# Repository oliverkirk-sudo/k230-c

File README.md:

# k230-c

## 当前检查点：已恢复 v12 + R2.1 源工程

本仓库保存 CM-K230 核心板的可编辑源工程和验证证据。v12 基线与 R2.1 累积增量均已恢复并核验。**这是原理图/候选封装恢复检查点，不是生产版本。当前候选仍没有完整核心板 PCB。**

当前入口：`project/cad/recovery-physical-candidate/CMK230_Core_REVIEW.kicad_pro`（原理图同名 `.kicad_sch`）。保持 `project/` 内相对目录结构即可解析已恢复的 10 个封装库。

## 本次重新验证（2026-10-03，KiCad 9.0.2）

- v12 ZIP：888 个成员 CRC 通过，886 个原始保留文件哈希匹配；SHA-256 `63dab93b8433b3a367571ec64b11568b9c81dc466e8d562ce2108b647d341e58`
- R2.1 ZIP：332 个成员 CRC 通过，325 个增量文件哈希匹配；SHA-256 `4e23cf611b37900dab169f0b44da5974ae70c65bbcf7624c97ccb16688eb3b5b`
- 增量在独立 v12 工作副本上通过防覆盖校验后应用，全部 325 个增量文件保持一致
- 新导出网表：254 个元件、1,509 个引脚绑定，与 R2.1 归档的元件、属性、网络、引脚功能和类型一致
- 恢复后新 ERC：0 个错误、0 个警告；10 个封装库均能解析
- R528 保持默认 DNP，存储默认禁止；149 个元件有封装字段，105 个仍未分配。R574 封装尚未完成验证

新结果在 `validation/2026-10-03-restored/`。`validation/2026-10-03-delta-only/` 保存基线尚未到达时的历史检查（0 错误、150 个缺库警告）；这些缺库警告已由完整恢复后的新结果取代。`project/` 中其他报告保留历史阶段含义，不能视为本次全部重新执行。

## 尚未完成的工程资格验证

- 当前 `recovery-physical-candidate` 没有完整核心板 PCB；历史 PCB、8 层试验和封装/负控夹具仍保留用于追溯，不是当前 6 层成品
- 38 × 38 mm 外形、140 个触点、1 mm 间距、恰好 6 个铜层及仅顶面贴装是设计要求，并非已达成的制造验收
- 尚需完成封装缺口、整板布局布线、DDR/时序、高温/上电、DFM 和工厂工艺确认
- TI 候选阻焊桥名义 80 µm；NXP 示例名义 55 µm。KiCad 全局最小阻焊桥设为 75 µm 时可能合并开窗。必须核对实际 CAM 与铜/蚀刻/阻焊/钢网/贴装能力

## 发布内容、来源与完整性

`project/` 保留源 CAD、库、脚本、数据、网表、工程审查和来源 URL/哈希，以及必要的 `LICENSE-01studio.txt` 上游 MIT 版权许可声明。未将该许可扩展为对其他第三方材料的新授权。

本公开源文件检查点经过筛选，未包含厂商 PDF/扫描页面、图像、运行时缓存、会话设置、日志、备份 ZIP 及部分大型历史 DDR 搜索生成结果。它不是两个原始 ZIP 的逐字节镜像。历史报告和冻结清单可能引用这些省略文件；需要相关生成结果的旧测试须先重新生成。完整排除项/原始哈希/两处非技术署名编辑见 `PUBLICATION_PROVENANCE.json`；当前发布文件完整性以根目录 `SHA256SUMS` 为准。

## English summary

The verified v12 baseline plus R2.1 delta has been restored. The active editable schematic resolves all 10 footprint libraries. Fresh KiCad 9.0.2 ERC has zero errors and zero warnings; the exported 254-component / 1,509-binding graph matches R2.1. There are 149 assigned and 105 unassigned component footprints. This is a source-recovery checkpoint, not a production release: no complete active six-layer board has been recovered or routed. Historical trials and tests retain their original limited scope.

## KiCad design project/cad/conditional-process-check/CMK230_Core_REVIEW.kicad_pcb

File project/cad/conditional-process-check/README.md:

# Separate conditional process model

This duplicates the current partial/unplaced import for an explicit rule experiment. It is not the production board or an accepted manufacturing recipe. The original 0.20mm-default diagnostic remains in ../high-temp-candidate/partial-pcb-drc-parity.json.

General copper clearance and minimum track width are 0.1016mm. Exactly30 enumerated pad pairs,15 each in U22 and U23, have a0.0762mm conditional pad-to-pad clearance based on source YCG geometry and published advanced process capability. No pad-to-track or arbitrary adjacent copper receives that allowance. The source lands have0.085mm nominal separation, only8.8µm above the proposed local minimum; etch tolerance, mask registration, stencil, assembly and the combined stack/castellation process require acceptance.

The model reports0 geometry violations while retaining138 unrouted items and199 reported missing-footprint issues. The complete source import ledger contains216 missing references. No severity or exclusion was changed. Positive controls confirm both a deliberately intruding listed pad pair and a foreign nearby track are still rejected by their intended rules.

Published advanced fine-line conditions do not automatically apply to the proposed1oz stack or guarantee manufacturing tolerance. Use process-model-manifest.json for exact assumptions and ../engineering references from the project root for the source evidence. Do not treat this as a finished-board DRC pass.

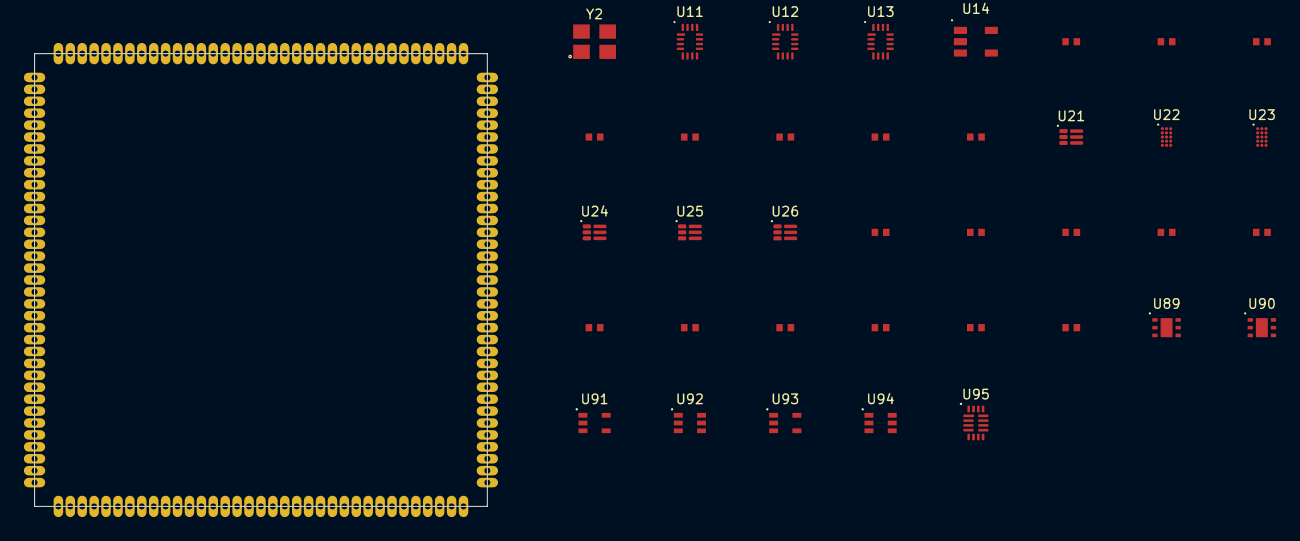
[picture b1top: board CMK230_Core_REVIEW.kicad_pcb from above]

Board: 8 copper layers, 38 parts (0 on the bottom side), 34 nets, no tracks yet.

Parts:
J1: CM-K230 edge contract ONLY; CMK230_38x38_140P1_D0.50_Oval0.80x1.80_PROCESS_UNQUALIFIED
R63, R64, R65, R66: 240R TNPW0402 0.1pct 10ppm TOTAL<=0.70pct CANDIDA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; Vishay_TNPW0402_IPC7351_SourceLand_PROCESS_CANDIDATE
R67, R68: 30k TNPW0402 0.1pct 10ppm TOTAL<=0.70pct CANDIDATE; Vishay_TNPW0402_IPC7351_SourceLand_PROCESS_CANDIDATE
R69, R70, R71: 200R TNPW0402 0.1pct 10ppm TOTAL<=0.70pct CANDIDA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; Vishay_TNPW0402_IPC7351_SourceLand_PROCESS_CANDIDATE
R201: 3.32k TNPW0402 0.1pct 10ppm TOTAL<=0.70pct CANDID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; Vishay_TNPW0402_IPC7351_SourceLand_PROCESS_CANDIDATE
R202, R208, R211, R214, R526: 10k TNPW0402 0.1pct 10ppm TOTAL<=0.70pct CANDIDATE; Vishay_TNPW0402_IPC7351_SourceLand_PROCESS_CANDIDATE
R207: 8.66k TNPW0402 0.1pct 10ppm TOTAL<=0.70pct CANDID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; Vishay_TNPW0402_IPC7351_SourceLand_PROCESS_CANDIDATE
R210: 20k TNPW0402 0.1pct 10ppm TOTAL<=0.70pct CANDIDATE; Vishay_TNPW0402_IPC7351_SourceLand_PROCESS_CANDIDATE
R213: 45.3k TNPW0402 0.1pct 10ppm TOTAL<=0.70pct CANDID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; Vishay_TNPW0402_IPC7351_SourceLand_PROCESS_CANDIDATE
R525: 88.7k TNPW0402 0.1pct 10ppm TOTAL<=0.70pct CANDID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; Vishay_TNPW0402_IPC7351_SourceLand_PROCESS_CANDIDATE
U11, U12, U13: TMUX1574RSVR / CANDIDATE; TI_RSV0016A_TMUX1574_1.8x2.6_P0.4_DrawingVerified
U14: SN74LVC1G32DBVR; TI_DBV0005A_SN74LVC1G32_SOT23_5_DrawingVerified
U21: TPS62827ADMQ; TI_DMQ0006A_TPS6282xA_1.5x1.5_SMD_DrawingVerified
U22, U23: TPS628640BYCGR; TI_YCG0015_TPS628640_1.05x1.78_P0.35_SMD_DrawingVerified
U24, U26: TPS62826ADMQ; TI_DMQ0006A_TPS6282xA_1.5x1.5_SMD_DrawingVerified
U25: TPS62825ADMQ; TI_DMQ0006A_TPS6282xA_1.5x1.5_SMD_DrawingVerified
U89: TPS3808G01DRVR VIN GUARD; TI_DRV0006A_D_TPS3808_6P_EP7_DrawingVerified_CANDIDATE
U90: TPS3808G01DRVR RESET DELAY; TI_DRV0006A_D_TPS3808_6P_EP7_DrawingVerified_CANDIDATE
U91: 74AUP1G17GW,125 HIGH_TEMP CANDIDATE; Nexperia_SOT353-1_AUP1G17_06_DrawingVerified_CANDIDATE
U92, U94: 74AUP1G97GW,125 HIGH_TEMP CANDIDATE; Nexperia_SOT363-2_AUP1G97_DrawingVerified_CANDIDATE
U93: 74AUP1G06GW,125 HIGH_TEMP CANDIDATE; Nexperia_SOT353-1_AUP1G17_06_DrawingVerified_CANDIDATE
U95: NVT4858HKZ TF HS50 CANDIDATE; NXP_SOT1161-2_NVT4858HK_1.8x2.6_P0.4_DrawingVerified_CANDID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
Y2: X322524MOB4SI 24MHz CL12pF CANDIDATE; YXC_X322524MOB4SI_3225_4P_DrawingCandidate

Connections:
CORE_PGOOD_5V: U21.2, U22.E1, U23.E1, U24.1, U25.1, U26.1
DDR_VREF: R65.2, R66.1
DISABLE_OR_TF: U13.13, U14.4
FB_1V8: R210.2, R211.1, U25.3
FB_3V3: R213.2, R214.1, U26.3
FB_CORE: R201.2, R202.1, U21.3
FB_DDR: R207.2, R208.1, U24.3
FIXED_RAILS_PGOOD_3V3: U24.2, U25.2, U26.2, U89.6, U92.3, U94.3
GLOBAL_DISABLE: U11.13, U12.13, U14.1, U93.4
GND: J1.1, J1.2, J1.3, J1.36, J1.49, J1.57, J1.64, J1.71, J1.78, J1.89, J1.106, R64.2, R66.2, R69.2, R70.2, R71.2, R202.2, R208.2, R211.2, R214.2, R526.2, U11.6, U12.6, U12.8, U12.10, U12.11, U12.12, U13.1, U13.4, U13.6, U13.8, U13.11, U13.15, U14.3, U21.4, U22.A1, U22.B1, U22.B2, U22.B3, U23.A1, U23.B1, U23.B2, U23.B3, U24.4, U25.4, U26.4, U89.5, U89.7, U90.5, U90.7, U91.3, U92.1, U92.2, U93.3, U94.1, U94.2, U95.7, Y2.2, Y2.4
MODE_TF: U11.15, U12.15, U14.2
RESET_DELAYED_1V8: U90.6, U91.2
RESET_RELEASE_REQUEST_1V8: U90.4, U94.4
RSTN: J1.122, U94.6
STORAGE_ENABLE_1V8: U92.4, U93.2
SW_CPU: U22.C1, U22.C2, U22.C3
SW_KPU: U23.C1, U23.C2, U23.C3
TFCARD_CLK: J1.21, U95.8
TFCARD_CMD: J1.22, U95.13
TFCARD_D0: J1.17, U95.10
TFCARD_D1: J1.18, U95.9
TFCARD_D2: J1.19, U95.12
TFCARD_D3: J1.20, U95.11
TF_HOST_CLK: U11.1, U95.5
TF_HOST_CMD: U11.4, U95.16
TF_HOST_D0: U11.8, U95.3
TF_HOST_D1: U11.11, U95.4
TF_HOST_D2: U12.1, U95.1
TF_HOST_D3: U12.4, U95.2
VDD1P1_DDR_IO: R63.2, R65.1, R207.1
VDD1P8: J1.8, R210.1, U89.1, U89.4, U90.1, U90.2, U91.5, U92.5, U93.5, U94.5, U95.15
VDD_3V3: J1.7, R213.1, U11.14, U12.14, U13.14, U14.5, U95.14
VIN_5V: J1.4, J1.5, J1.6, R67.1, R68.1, R525.1, U21.6, U22.D1, U22.D2, U22.D3, U23.D1, U23.D2, U23.D3, U24.6, U25.6, U26.6
VIN_GUARD_SENSE: R525.2, R526.1, U89.2

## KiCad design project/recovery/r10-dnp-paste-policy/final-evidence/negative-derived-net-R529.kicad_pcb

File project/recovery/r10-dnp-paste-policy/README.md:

# DNP stencil export policy review

**Result: PASS_REVIEW_ONLY on KiCad 9.0.2+dfsg-1.** The installed Gerber CLI and Python plot API do not expose a paste-specific “suppress DNP” option. A reversible, separately named assembly-board derivation successfully removes DNP paste while preserving copper, mask, holes, electrical bindings, placement and population attributes. This review does not qualify a stencil, assembly process, or production release.

## Installed controls and evidence

The local `kicad-cli pcb export gerbers --help` exposes these DNP controls:

- `--hide-DNP-footprints-on-fab-layers`
- `--sketch-DNP-footprints-on-fab-layers`
- `--crossout-DNP-footprints-on-fab-layers`

Their names and help scope them to fabrication layers. The installed `PCB_PLOT_PARAMS` has corresponding `Get/SetHideDNPFPsOnFabLayers`, `Get/SetSketchDNPFPsOnFabLayers` and `Get/SetCrossoutDNPFPsOnFabLayers` methods, but no DNP paste filter. `FOOTPRINT.IsDNP/SetDNP`, BOM/PnP exclusion flags, `PAD.Get/SetLayerSet`, and `LSET.RemoveLayer` are separate APIs. Position export independently has `--exclude-dnp`.

The installed evidence is retained in [Gerber help](final-evidence/gerbers-help.txt), [position help](final-evidence/pos-help.txt), and [API inventory](final-evidence/installed-api.json). The [official KiCad 9 CLI documentation](https://docs.kicad.org/9.0/en/cli/cli.html) corroborates the documented scope. The conclusion is bounded to the inspected 9.0.2 runtime, not other KiCad releases or third-party exporters.

Actual default CLI, hide-on-Fab CLI, combined Fab controls, and native Python `SetHideDNPFPsOnFabLayers(True)` plotting all retain the same DNP paste flashes in the fixture. In this build the tested CLI hide flag also left the fixture Fab output unchanged; this review does not claim that those Fab controls were effective or diagnose that separate behavior.

## Population source and immutable inputs

Authoritative inputs are the supplied project's `cad/recovery-physical-candidate/master.xml` and `tools/population_contract.py`. Their hashes and the source footprint-library hashes are in [results.json](final-evidence/results.json). The master marks **JP1, R45, R47 and R528 DNP**. JP1, J1, TP81 and TP82 are fabricated features in the population contract.

DNP is taken from the native master property and reconciled against board attributes, not inferred from value text, a generic BOM exclusion, or a reference prefix. Native BOM/PnP/board-only attribute parity, footprint library identity and every numbered electrical pad/net binding must agree with the master before derivation and on the derived board. Reference coverage alone is never sufficient electrical parity. Duplicate references, duplicate/ambiguous population properties, and unexplained board/master differences are errors. The master symbol pin declarations must exactly match its net-node pin set. Every included footprint must contain all expected numbered electrical pads, with no unknown numbers; each native pad must carry the exact expected net name. Multiple physical pads with one number are allowed only when every copy matches that same expected net. Both source and derived boards undergo these checks, including when subset-fixture mode is enabled.

The current master explicitly supplies a net node for every declared symbol pin, including NC pins. There are no NC or virtual-pin exceptions in this policy. An NC pad with an explicit master net must match that net; an importer that substitutes net zero needs a separately reviewed explicit rule. Missing master nodes, implicit virtual pins and unrecognized numbered mechanical pads fail closed rather than being guessed. File-level checks also reject electrical identity on non-copper pads and nonzero net declarations on unnumbered pads before native KiCad can normalize those declarations away.

The published master, population contract and footprint-library sources remained byte-identical. No published main-board or current R8 CAD was edited. The fixture deliberately represents only eight master references; the 246 absent references are explicitly reported, not silently treated as complete coverage.

## Derived-board procedure

1. Pin a source board, master XML and population contract by SHA-256. Keep the source as the canonical design. Require complete master reference coverage and exact per-reference pin/net parity by default; `--allow-subset-fixture` is an explicit review-only exception.
2. Generate a new, separately named native `.kicad_pcb` file. The helper refuses to overwrite the source or an existing output. Do not update footprint libraries, run footprint replacement, recalculate placement, or refill zones.
3. For each reconciled DNP footprint, remove only `F.Paste` and `B.Paste` layer membership from pads that retain other layers. Preserve the pad number, UUID, copper geometry, net, mask settings, position and every other field.
4. Remove a paste-only pad object only when it has no number, net declaration or drill. The CRCW0201 source footprint uses two such standalone apertures, so removing paste from its numbered copper pads alone would do nothing. Numbered/net-bound/drilled paste-only objects fail for review instead of being discarded.
5. Remove footprint-owned paste-only graphics from DNP footprints. All other footprint tokens remain unchanged. Paste-layer properties, zones, wildcard paste layers, unowned board paste, and groups referencing removed apertures fail closed for ownership/format review. These unsupported constructs are not guessed or silently dropped.
6. Reject paste on any contract-declared bare fabricated feature, including JP1 and TP81/TP82. A missing fitted-part aperture is likewise an error, not an acceptable side effect.
7. Verify that all remaining native board tokens exactly match the expected allowed-only edit; reload with native KiCad; check that DNP pads, graphics, fields and zones have no native paste membership; confirm native save/reload preserves the edit. Keep hashes and a per-object change manifest. Source and derived pin/net checks are independent of the allowed-only token comparison, so faithfully preserving a wrong source net does not pass.
8. Export **only F.Paste and B.Paste from the derived board** for the population variant. Continue taking copper, solder mask, outline and drill deliverables from the canonical source. Preserve the existing reconciled BOM/PnP process independently. Regenerate the derived artifact whenever the board, population variant, library binding or source contract changes.

The helper uses a bounded native S-expression patch instead of a full-board rewrite for the initial derivation. This preserves every non-paste token verbatim; KiCad itself then loads, saves and plots the result. A whitespace-insensitive token comparison allows native formatting while rejecting changes to values. The source plus the manifest makes the operation reversible: discard the derived board and regenerate; never copy it back into the canonical project.

R528 remains DNP and placement-excluded, and its original separated copper/net assignments remain unchanged. Removing its paste is one assembly safeguard; maintaining its electrical inhibit also requires the no-fit assembly instruction and the existing electrical/interlock review. This fixture does not certify circuit behavior.

## Reproduced results

The small two-sided fixture loads the existing source-library CRCW0201, bare bridge and bare testpad geometry. It adds clearly synthetic paste graphics/apertures, a mixed copper/paste pad case, a same-number/same-net plated-hole pad on TP81, track and via to exercise export semantics. The TP81 duplicate pad is a deliberate fixture control, not a source footprint-library change. Original numbered pads retain their authoritative master pin-net bindings; R528 retains VDD1P8 on pin 1 and BOOT_VOLTAGE_QUALIFIED_1V8 on pin 2, plus DNP and placement exclusion. It is not a production layout or a replacement netlist.

| Measurement | Default / Fab hide | Derived stencil |
|---|---:|---:|
| F.Paste flashes | 9 | 3 |
| B.Paste flashes | 7 | 3 |
| F.Paste component attribution | DNP and fitted | R529 only |
| B.Paste component attribution | DNP and fitted | R46 only |
| Fitted paste graphic regions | 1 per side | 1 per side |

Each surviving side has the fitted resistor's two source-library apertures plus one synthetic test aperture. The tested default DNP paste includes intentionally added test geometry; these counts must not be quoted as production-board aperture counts.

All **42 checks** pass, including sixteen intentional rejected controls:

- Copper deletion from R528 is rejected
- Fitted R529 aperture loss is rejected
- Paste added to bare TP81 is rejected for the bare-feature rule
- R528 board DNP-attribute removal is rejected
- R528 master-DNP removal is rejected independently
- Unowned board-level paste is rejected
- Wrong-net R528 and fitted R529 pads are rejected independently on source and derived boards (four controls)
- Missing R528 numbered pads and unknown TP81 pad numbers are rejected
- A duplicate-number TP81 pad with the wrong net is rejected, while both same-net copies pass
- A nonzero net declaration on an unnumbered pad is rejected
- Non-paste footprint position changes are rejected by the allowed-only token comparison
- A master missing a declared pin's net node is rejected without inventing an NC/virtual exception

Full F.Cu, B.Cu, F.Mask, B.Mask, Edge.Cuts and F.Fab Gerber content compares equal after removing only creation timestamp, file identity and checksum metadata. Excellon drill geometry compares equal after timestamp removal. Default PnP CSV is byte-identical and contains only fitted R46 and R529; DNP and bare features remain excluded. BOM attributes and master inputs are unchanged; no independent purchasing BOM regeneration is claimed.

The manifest records 14 unique expected pins and 15 numbered physical pads for the eight-reference fixture. This includes the deliberate same-number TP81 duplicate. It records an empty NC/virtual exception list. The results file also pins both executed Python scripts by SHA-256.

Machine-readable evidence: [checks and hashes](final-evidence/results.json), [per-object derivation manifest](final-evidence/derivation.json), [derived native board](final-evidence/DERIVED_STENCIL_REVIEW_ONLY.kicad_pcb), [native roundtrip](final-evidence/NATIVE_ROUNDTRIP_REVIEW_ONLY.kicad_pcb). Negative fixtures are deliberately invalid and must never be used as manufacturing inputs.

## Reproduce with parameterized paths

Requires the installed KiCad CLI and the Python interpreter that provides `pcbnew` (here `/usr/bin/python3`). No additional package installation is required. The output directory must be new.

```sh
/usr/bin/python3 test_policy.py --project "$PROJECT_ROOT" --out "$REVIEW_RUN_DIR"
```

Run an independent review derivation on a complete board:

```sh
/usr/bin/python3 derive_assembly_paste.py \
  --source "$SOURCE_BOARD" \
  --output "$DERIVED_BOARD" \
  --master "$MASTER_XML" \
  --population-contract "$POPULATION_CONTRACT" \
  --report "$DERIVATION_REPORT"

kicad-cli pcb export gerbers \
  --layers F.Paste,B.Paste \
  --output "$STENCIL_REVIEW_DIR/" \
  "$DERIVED_BOARD"
```

Supply only trusted project code as the population-contract argument. For a deliberately incomplete isolated fixture, explicitly add `--allow-subset-fixture`. To recheck an existing derived board, use `--verify-only` and a new report destination.

**Boundary:** CAD export policy is demonstrated for the supported constructs on this runtime. There is no claim about stencil thickness, area ratio, transfer efficiency, paste chemistry, print registration, mask-process limits, reflow or assembly yield. Those require a separate manufacturing/process review. No vendor was contacted and no production output was issued.

## R10 integration on the recovered project

R10 adds only this review/tool directory to exact published R9. Every existing project file remains byte-identical: the circuit revision remains RCV-R9, with221 assigned footprints and33 gaps. The42-check fixture suite was rerun against this exact project, not merely copied from the earlier R7 review.

The actual recovered R7 ten-reference native fixture was also tested. It uses an Audit_Footprints library alias, which strict source/master checking initially rejected as intended. A separate copy normalizes only those ten FPID strings after confirming every copied .kicad_mod is byte-identical to its authoritative current library file. The original fixture is preserved. This does not waive electrical parity.

[test_recovered_fixture.py](test_recovered_fixture.py) reproduces that normalization and derivation using explicit --project and --out arguments. [The actual-fixture result](recovered-fixture/recovered-fixture-results.json) confirms copper/mask18→18 flashes and paste14→12, removing only R528's two apertures. All non-paste CAM layers remain equal; all numbered pad/net identities and population flags agree with the current master. This is a recovered fixture, not the complete core board.

The synthetic two-sided fixture deliberately exercises both front and back paste. It does not change the user's top-only core assembly requirement. Deliberately corrupted negative fixtures and all diagnostic Gerbers are review artifacts, never production inputs. The bounded export-policy defect is addressed by the verified derivation, while full-board application and stencil/process qualification remain open.

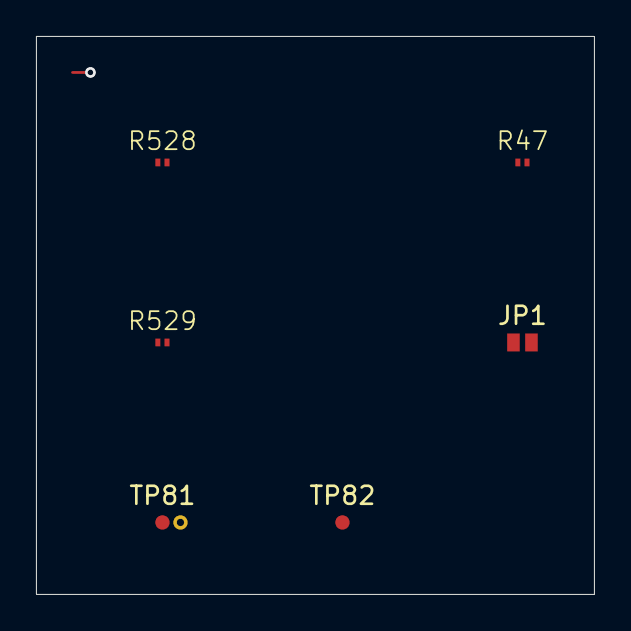
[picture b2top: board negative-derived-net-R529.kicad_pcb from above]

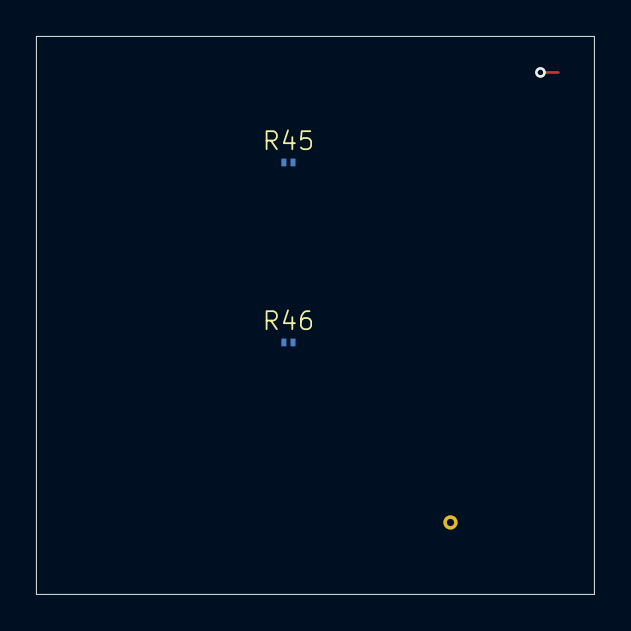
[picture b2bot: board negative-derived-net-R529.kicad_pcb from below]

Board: 2 copper layers, 31.0 x 31.0 mm, 8 parts (2 on the bottom side), 3 nets.

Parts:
JP1: OPEN=EMMC / CLOSED=TF; COLD ONLY; Core_Cold_Selector_Open_SolderBridge_CANDIDATE
R45: 10k BOOT0 HIGH / DNP; Vishay_CRCW0201_SourceLand_PROCESS_CANDIDATE
R46: 10k BOOT1 HIGH; Vishay_CRCW0201_SourceLand_PROCESS_CANDIDATE
R47: 10k BOOT1 LOW / DNP; Vishay_CRCW0201_SourceLand_PROCESS_CANDIDATE
R528: 0R QUALIFICATION STRAP DNP; Vishay_CRCW0201_SourceLand_PROCESS_CANDIDATE
R529: 100k DEFAULT INHIBIT; Vishay_CRCW0201_SourceLand_PROCESS_CANDIDATE
TP81: PMU OUT0 OBSERVE ONLY; Core_PMUSTATUS_Top_TestPad_0p8_CANDIDATE
TP82: PMU OUT1 OBSERVE ONLY; Core_PMUSTATUS_Top_TestPad_0p8_CANDIDATE

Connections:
BOOT1: R46.1, R47.1
BOOT_VOLTAGE_QUALIFIED_1V8: R528.2, R529.1
VDD1P8: R45.2, R46.2, R528.1, R529.2
